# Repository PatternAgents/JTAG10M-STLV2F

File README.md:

JTAG10M-STLV2F
==============

ST-Link/V2 to JTAG 10 Pin Male Adapter

[  
*PatternAgents JTAG10M-STLV2F*](http://www.patternagents.com/projects/JTAG10M-STLV2F.html)

The PatternAgents.

Features:

[  
*Licensing CC BY-NC-SA 4.0*](http://creativecommons.org/licenses/by-nc-sa/4.0/)

PatternAgents uses the increasingly popular business model called "Dual Licensing" 
in which both the open source software distribution mechanism and traditional commercial software distribution models are combined.

Open Source Projects:        

If you are developing and distributing open source applications under the Creative Commons CC BY-NC-SA 4.0, 
as published by the Creative Commons Foundation, then you are free to use the PatternAgents hardware/software under the CC BY-NC-SA 4.0 license. 
Please note that CC BY-NC-SA 4.0 requires that all modifications to the original code as well as all Derivative Works 
must also be released under the terms of the CC BY-NC-SA 4.0 license.

Closed Source Projects:

If you are developing and distributing traditional closed source or commercial applications, 
you must purchase a PatternAgents commercial use license, 
which is specifically designed for users interested in retaining the proprietary status of their designs and code. 
All PatternAgents commercial licenses expressly supersede the CC BY-NC-SA 4.0 license. 
This means that when you license the PatternAgents software under a commercial license, 
you specifically do not use the software under the CC BY-NC-SA 4.0 license and therefore you are not subject to any of its terms.
        
If you would like to use our designs for your own personal or educational use, have at it! 

Our public design repository is available at <a href="https://github.com/patternagents">Github</a>.

If you would like to produce our designs for commercial use, or as products for sale, 
please contact us to arrange for a Commercial Use license. We have many other designs, 
as well as options and extras that are not released publicly. 
We will also customize designs, firmware, and software for a reasonable fee, just contact us to discuss your requirements.

THIS SOFTWARE IS PROVIDED BY THE CONTRIBUTORS "AS IS" AND WITHOUT ANY EXPRESS OR IMPLIED WARRANTIES, 
INCLUDING, BUT NOT LIMITED TO, THE IMPLIED WARRANTIES OF MERCHANTABILITY AND FITNESS FOR A PARTICULAR PURPOSE ARE DISCLAIMED. 
IN NO EVENT SHALL THE COPYRIGHT OWNER OR CONTRIBUTORS BE LIABLE FOR ANY DIRECT, INDIRECT, INCIDENTAL, SPECIAL, EXEMPLARY, 
OR CONSEQUENTIAL DAMAGES (INCLUDING, BUT NOT LIMITED TO, PROCUREMENT OF SUBSTITUTE GOODS OR SERVICES; LOSS OF USE, DATA, 
OR PROFITS; OR BUSINESS INTERRUPTION) HOWEVER CAUSED AND ON ANY THEORY OF LIABILITY, WHETHER IN CONTRACT, 
STRICT LIABILITY, OR TORT (INCLUDING NEGLIGENCE OR OTHERWISE) ARISING IN ANY WAY OUT OF THE USE OF THIS SOFTWARE, 
EVEN IF ADVISED OF THE POSSIBILITY OF SUCH DAMAGE. 

-------------------------------------------------------------------------------------------

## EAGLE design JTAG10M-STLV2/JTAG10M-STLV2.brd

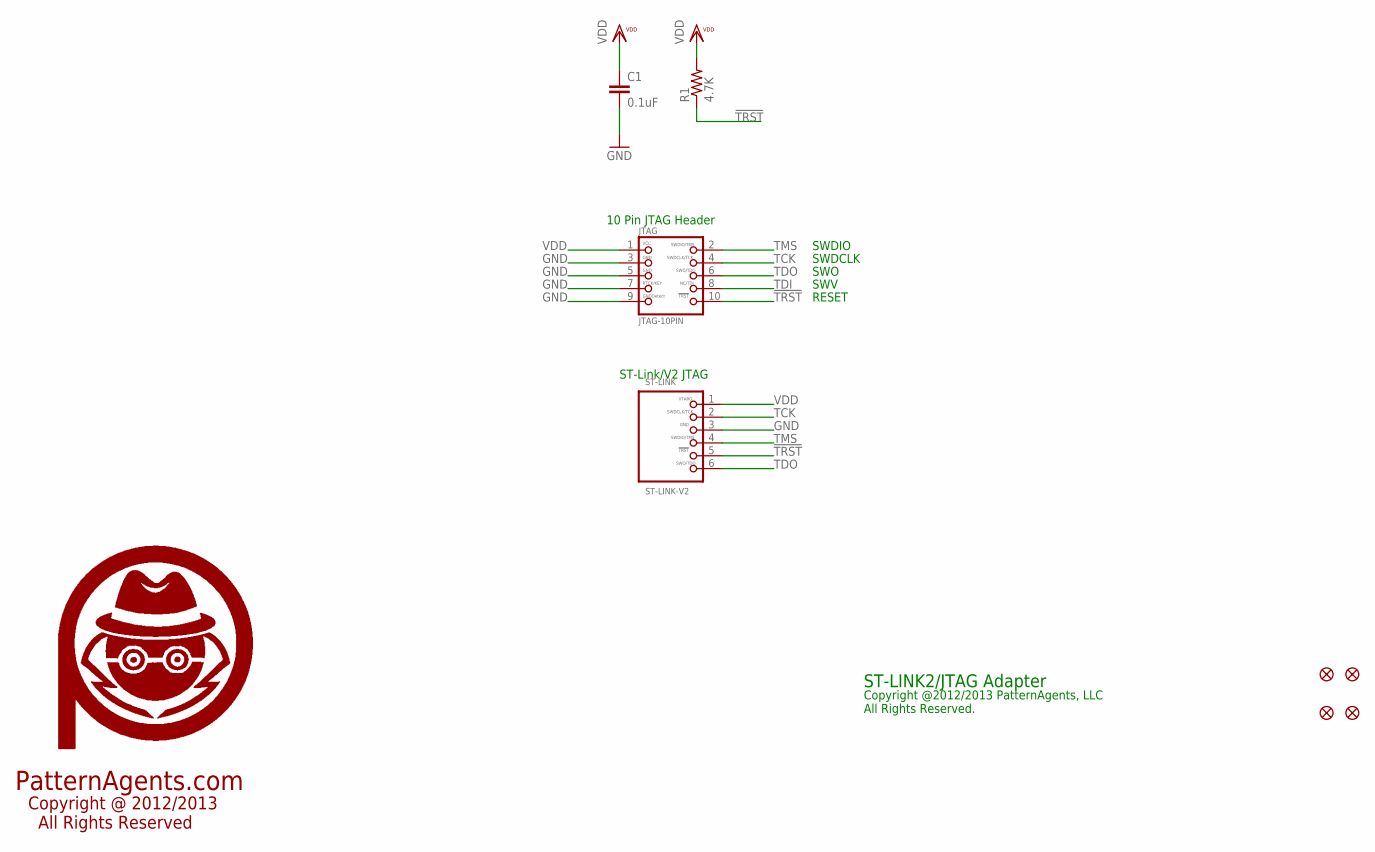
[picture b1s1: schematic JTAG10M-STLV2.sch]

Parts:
C1: 0.1uF; 0603-CAP
FID1, FID2, FID3, FID4: FIDUCIAL1.5X3; FIDUCIAL-1.5X3
JTAG: JTAG-10PIN; 2X05_1.27MM_SMT
R1: 4.7K; 0603-RES
ST-LINK: ST-LINK-V2; 1X06_2.54MM_PTH
U$2: PA_LOGO_SYMLARGE; PA_LOGO_AGENT_LRG_SYM

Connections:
!TRST: JTAG.10, R1.1, ST-LINK.5
GND: C1.2, JTAG.3, JTAG.5, JTAG.7, JTAG.9, ST-LINK.3
TCK: JTAG.4, ST-LINK.2
TDI: JTAG.8
TDO: JTAG.6, ST-LINK.6
TMS: JTAG.2, ST-LINK.4
VDD: C1.1, JTAG.1, R1.2, ST-LINK.1

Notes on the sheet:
PatternAgents.com
Copyright @ 2012/2013 All Rights Reserved
ST-LINK2/JTAG Adapter
Copyright @2012/2013 PatternAgents, LLC All Rights Reserved.
SWDIO
SWDCLK
RESET
10 Pin JTAG Header
SWO
SWV
ST-Link/V2 JTAG

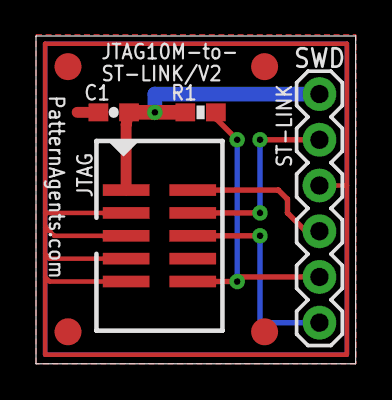
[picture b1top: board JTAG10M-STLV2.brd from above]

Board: 2 copper layers, 17.8 x 18.2 mm, 9 parts (1 on the bottom side), 6 nets.

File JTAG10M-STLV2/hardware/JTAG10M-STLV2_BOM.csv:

"Part";"Value";"Device";"Package";"Description";"";
"C1";"0.1uF";"CAP0603-CAP";"0603-CAP";"Capacitor";"";
"FID1";"FIDUCIAL1.5X3";"FIDUCIAL1.5X3";"FIDUCIAL-1.5X3";"Fiducial Alignment Points";"";
"FID2";"FIDUCIAL1.5X3";"FIDUCIAL1.5X3";"FIDUCIAL-1.5X3";"Fiducial Alignment Points";"";
"FID3";"FIDUCIAL1.5X3";"FIDUCIAL1.5X3";"FIDUCIAL-1.5X3";"Fiducial Alignment Points";"";
"FID4";"FIDUCIAL1.5X3";"FIDUCIAL1.5X3";"FIDUCIAL-1.5X3";"Fiducial Alignment Points";"";
"JTAG";"JTAG-10PIN";"JTAG-10PINSMD";"2X05_1.27MM_SMT";"JTAG 10 Pin (SWD) Programming Connector";"";
"R1";"4.7K";"RESISTOR_SFE0603-RES";"0603-RES";"Resistor";"";
"ST-LINK";"ST-LINK-V2";"ST-LINK-V2";"1X06_2.54MM_PTH";"ST-Link/V2 JTAG/SWD Connector";"";
"U$2";"PA_LOGO_SYMLARGE";"PA_LOGO_SYMLARGE";"PA_LOGO_AGENT_LRG_SYM";"PatternAgents Logo Symbol";"";

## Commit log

2014-04-17 add eagle files

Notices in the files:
parts and their libraries:
PatternAgents-Logos: License : http://creativecommons.org/licenses/by-sa/3.0
(Creative Commons 3.0)
